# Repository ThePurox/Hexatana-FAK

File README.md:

# Hexatana
Hexatana is a 36 katana-inspired keyboard designed around [hexagonal keycaps](https://hw.s-ol.nu/HEX-keycaps/), which require Choc v1 switches.
It uses the CH552T controller and [FAK firmware](https://github.com/semickolon/fak).

The electronic design is derived from the [MIAO MCU board](https://github.com/kilipan/miao).

# Buildguide
For soldering everything have a look at the [interactive bill of materials](bom/ibom.html).

After soldering everything plug in the switches into the hot swap sockets and install the keycaps.

Now it is time to configure the firmware.
All config-files needed for an extremely basic firmware to test whether all the keys work can be found [here](https://github.com/ThePurox/fak-config/tree/main/keyboards/hexatana)

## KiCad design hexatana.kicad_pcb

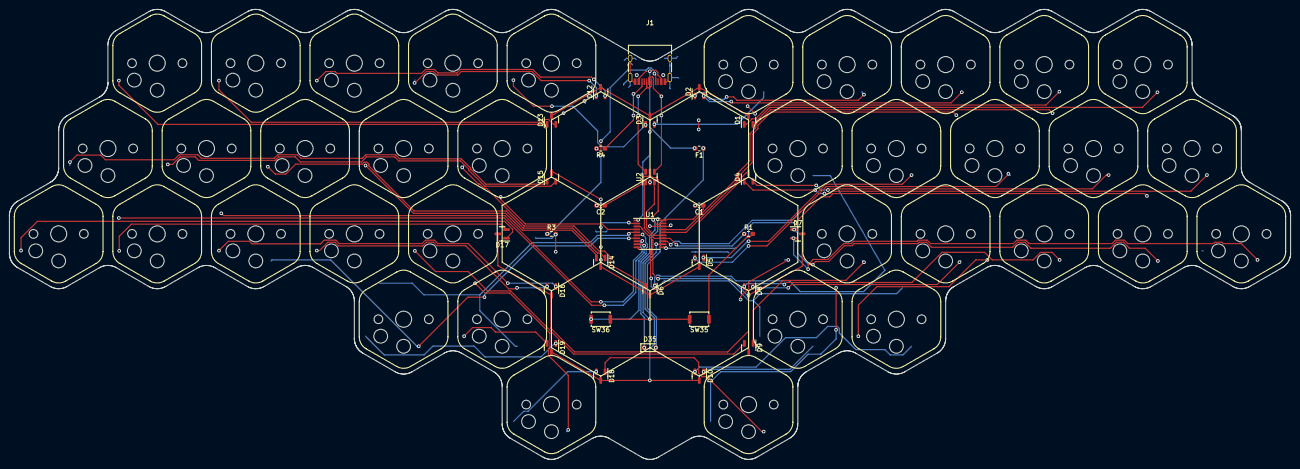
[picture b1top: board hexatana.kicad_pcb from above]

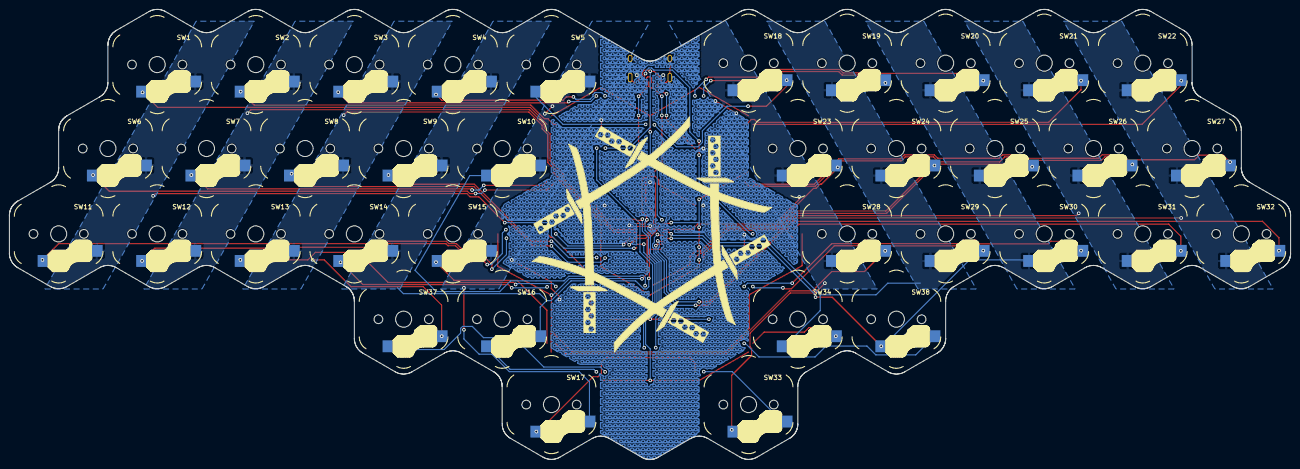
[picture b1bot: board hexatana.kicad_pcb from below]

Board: 2 copper layers, 279.5 x 98.2 mm, 66 parts (36 on the bottom side), 63 nets.

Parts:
C1, C2: 100nF; C_0603_1608Metric_Pad1.08x0.95mm_HandSolder
D1, D2, D3, D4, D5, D6, D7, D8, D9, D10, D12, D13, D14, D15, D16, D17, D18, D19: BAV70_Small; SOT-23
D35: PMEG2010EA; D_SOD-323_HandSoldering
F1: 500mA; Fuse_0603_1608Metric_Pad1.05x0.95mm_HandSolder
J1: USB_C_Receptacle_USB2.0; USB_C_Receptacle_HRO_TYPE-C-31-M-12
R1: 10k; R_0603_1608Metric_Pad0.98x0.95mm_HandSolder
R3, R4: 5.1k; R_0603_1608Metric_Pad0.98x0.95mm_HandSolder
SW1, SW2, SW3, SW4, SW5, SW6, SW7, SW8, SW9, SW10, SW11, SW12, SW13, SW14, SW15, SW16, SW17, SW18, SW19, SW20, SW21, SW22, SW23, SW24, SW25, SW26, SW27, SW28, SW29, SW30, SW31, SW32, SW33, SW34, SW37, SW38: SW_Push; PG1350_hotswap
SW35: BOOT; SW_Push_SPST_NO_Alps_SKRK
SW36: RESET; SW_Push_SPST_NO_Alps_SKRK
U1: TSSOP-20_4.4x6.5mm_P0.65mm
U2: USBLC6-2SC6; SOT-23-6

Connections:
+3.3V: C1.1, SW35.2, SW36.2, U1.20 (V33)
BOOT: R1.2, SW35.1
CC1: J1.A5 (CC1), R3.1
CC2: J1.B5 (CC2), R4.1
GND: C1.2, C2.2, J1.A1 (GND), J1.A12 (GND), J1.B1 (GND), J1.B12 (GND), J1.S1 (SHIELD), R3.2, R4.2, U1.18 (GND), U2.2 (GND)
unnamed: D1.1 (A1), SW2.2
unnamed: D1.2 (A2), SW1.2
unnamed: D2.1 (A1), SW4.2
unnamed: D2.2 (A2), SW3.2
unnamed: D3.1 (A1), SW18.1
unnamed: D3.2 (A2), SW5.2
unnamed: D4.1 (A1), SW6.2
unnamed: D4.2 (A2), SW7.2
unnamed: D5.1 (A1), SW9.2
unnamed: D5.2 (A2), SW8.2
unnamed: D6.1 (A1), SW10.2
unnamed: D6.2 (A2), SW23.1
unnamed: D7.1 (A1), SW12.2
unnamed: D7.2 (A2), SW11.2
unnamed: D8.1 (A1), SW14.2
unnamed: D8.2 (A2), SW13.2
unnamed: D9.1 (A1), SW15.2
unnamed: D9.2 (A2), SW28.1
unnamed: D10.1 (A1), SW16.2
unnamed: D10.2 (A2), SW37.2
unnamed: D12.1 (A1), SW19.1
unnamed: D12.2 (A2), SW20.1
unnamed: D13.1 (A1), SW22.1
unnamed: D13.2 (A2), SW21.1
unnamed: D14.1 (A1), SW25.1
unnamed: D14.2 (A2), SW24.1
unnamed: D15.1 (A1), SW27.1
unnamed: D15.2 (A2), SW26.1
unnamed: D16.1 (A1), SW30.1
unnamed: D16.2 (A2), SW29.1
unnamed: D17.1 (A1), SW32.1
unnamed: D17.2 (A2), SW31.1
unnamed: D18.1 (A1), SW17.2
unnamed: D18.2 (A2), SW33.1
unnamed: D19.1 (A1), SW38.1
unnamed: D19.2 (A2), SW34.1
unnamed: D35.2 (A), F1.1
PORT+: J1.A6 (D+), J1.B6 (D+), U2.6 (I/O1)
PORT-: J1.A7 (D-), J1.B7 (D-), U2.4 (I/O2)
RST: SW36.1, U1.6 (RST)
UDM: U1.15 (P3.7), U2.3 (I/O2)
UDP: R1.1, U1.14 (P3.6), U2.1 (I/O1)
VBUS: F1.2, J1.A4 (VBUS), J1.A9 (VBUS), J1.B4 (VBUS), J1.B9 (VBUS)
VCC: C2.1, D35.1 (K), U1.19 (VCC), U2.5 (VBUS)
col1: SW1.1, SW6.1, SW11.1, U1.11 (P3.3)
col2: SW2.1, SW7.1, SW12.1, U1.17 (P1.2)
col3: SW3.1, SW8.1, SW13.1, SW37.1, U1.16 (P1.3)
col4: SW4.1, SW9.1, SW14.1, SW16.1, U1.10 (P3.0)
col5: SW5.1, SW10.1, SW15.1, SW17.1, U1.13 (P3.5)
col6: SW18.2, SW23.2, SW28.2, SW33.2, U1.4 (P1.6)
col7: SW19.2, SW24.2, SW29.2, SW34.2, U1.5 (P1.7)
col8: SW20.2, SW25.2, SW30.2, SW38.2, U1.7 (P1.0)
col9: SW21.2, SW26.2, SW31.2, U1.8 (P1.1)
col10: SW22.2, SW27.2, SW32.2, U1.9 (P3.1)
row1: D1.3 (K), D2.3 (K), D3.3 (K), D12.3 (K), D13.3 (K), U1.1 (P3.2)
row2: D4.3 (K), D5.3 (K), D6.3 (K), D14.3 (K), D15.3 (K), U1.2 (P1.4)
row3: D7.3 (K), D8.3 (K), D9.3 (K), D16.3 (K), D17.3 (K), U1.3 (P1.5)
row4: D10.3 (K), D18.3 (K), D19.3 (K), U1.12 (P3.4)

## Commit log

2024-01-07 v 0.1
2024-01-08 fixed missing col5 on mcu
2024-01-28 v0.1
2024-05-28 added ibom and made readme more explicit
